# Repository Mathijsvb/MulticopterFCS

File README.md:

# About the project

MulticopterFCS is a flight controller build from the ground up. It is meant to be a development platform mainly focused on autonomous indoor flying of multi-rotor drones. 

> **Warning**
> The current version still contains design errors.

|Diagram|Board|
|---|---|
|||

# Key features

**On board:**
* High performance MCU (STM32H743 running up to 480 MHz)
* Accelerometer and gyro (MPU6000)
* Magnetometer (HMC5883L)
* Pressure and temperature sensor (BMP388)
* 64-Kbit of F-RAM (FM24C64B)
* 2x RGB LED

**Connectors:**

| **quantity** 	| **purpose**  	| **connector type**           	| **Comment**                                                           |
|----------	|----------	|--------------------------	|----------------------------------------------------------------------	|
| 1        	| SWD/JTAG 	| 1.27 mm pitch 10-pin     	| For programming and debugging                                        	|
| 1        	| SDIO     	| Micro SD Card            	| For logging data during the flight                                   	|
| 1        	| I²C      	| JST SH 4-pin             	| External I²C connector                                               	|
| 2        	| UART     	| JST SH 4-pin             	| External UART connector                                              	|
| 1        	| Battery  	| JST SH 2-pin             	| Used to measure battery voltage                                      	|
| 1        	| LED	  	| JST SH 8-pin             	| To control external LEDs                                      	|
| 1        	| IBUS     	| 2.54 mm pitch header     	| IBUS used by external receivers to communicate remote control signals |
| 6        	| PWM      	| 2.54 mm pitch header     	| PWM is used to control external ESC's                                	|
| 1        	| Buzzer   	| 2.54 mm pitch header     	| For connecting a buzzer                                              	|
| 1        	| RPLiDAR  	| 2.50 mm MOLEX SPOX 7-pin 	| This connector will be used for the RPLiDAR                          	|
| 2        	| USB      	| USB Mini B               	| USB1 goes directly to the MCU, USB2 gets converted to serial first   	|

# Roadmap:

1. ✔️ Project orientation
2. ✔️ Deciding on components
3. ✔️ Creating schematic
4. ✔️ Routing PCB
5. ✔️ Manufacturing the PCB
6.  Testing
	1. ✔️ Programming MCU
	2. ❌ Gyro/Accelerometer
		1.  ✔️ Find a the reason for to the Gyro/Accelerometer not working
		*   The MPU-6000 seems to need the ability to toggle CS which the current board does not support. Board revision is needed.
		2. Pick new Gyro/Accelerometer
	3. ❌ Magnetometer
		* Can't be detected with an I2C scanner, probably dead.
	4. Barometric pressure sensor
		1. ✔️ Check if it can be found with the I2C scanner.
		2. Check is values are sensible.
	5. ❌ On board F-RAM
		* Wrong IC choice on my part.
	6. ESC control
	7. IBUS communication
	8. Buzzer
	9. ✔️ LEDs
7. Writing drivers
	1. Gyro/Accelerometer
	2. Magnetometer
	3. Barometric pressure sensor
	4. On board F-RAM
	5. ESC control
	6. IBUS communication
	7. Buzzer and LEDs
	8. SD Card
	9. USB
8. Signal processing
	1. Data conversion and correction
	2. Data filtering
	3. Extended Kalman filter implementation for sensor fusion
	4. PI(D) controller
9. FSM controller 
10. Data logging on the SD Card

Future goals on the roadmap are likely to be Simultaneous Localization and Mapping using a LiDAR implementation. Based on this, autonomous indoor flight could be developed.

# Licensing

**This system is still a work in progress, use anything inside this repository at your own risk.**

This an open source project released under the BSD 3-Clause License.

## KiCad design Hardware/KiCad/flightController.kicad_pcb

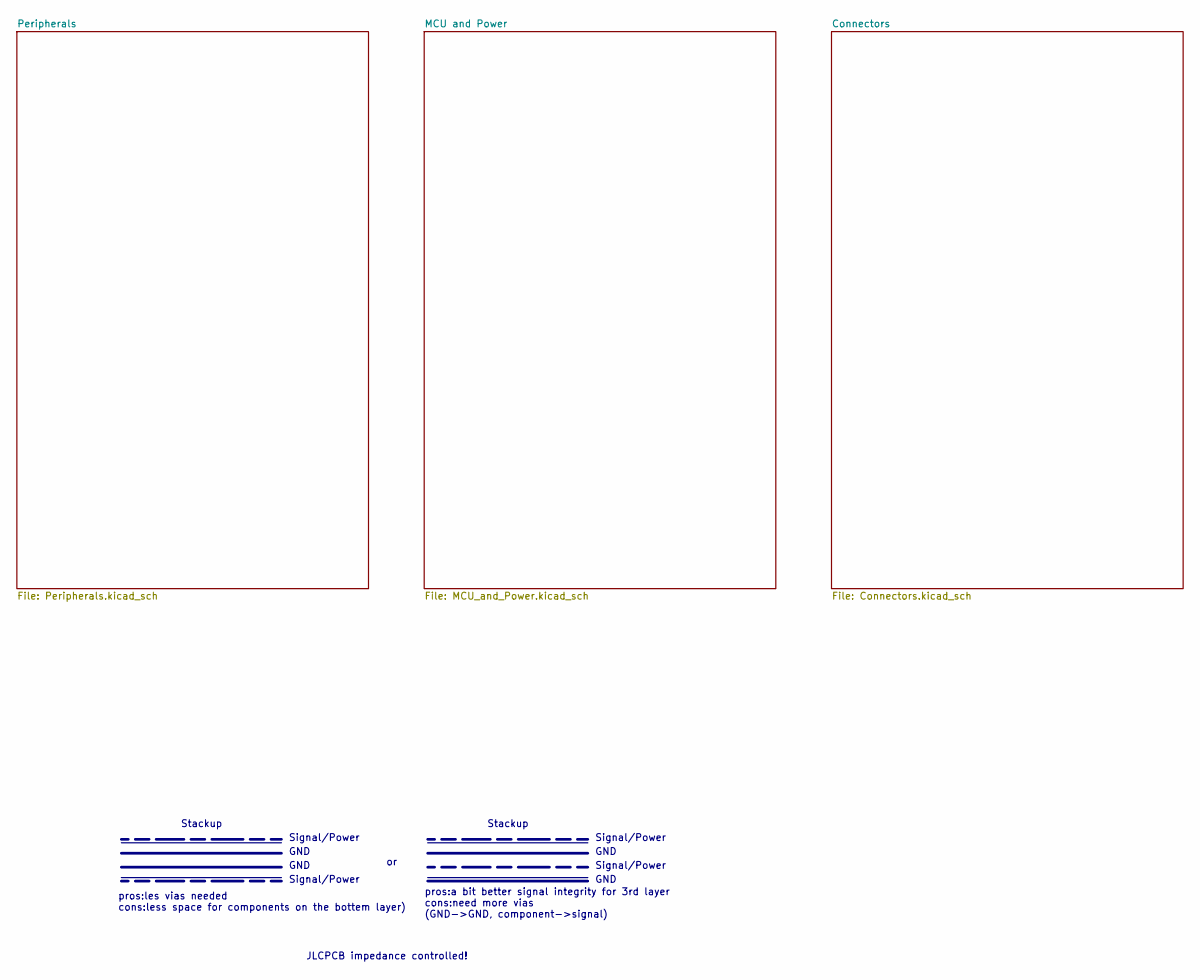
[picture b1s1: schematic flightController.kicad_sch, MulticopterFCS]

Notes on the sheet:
GND
Stackup
pros:les vias needed cons:less space for components on the bottem layer)
JLCPCB impedance controlled!
pros:a bit better signal integrity for 3rd layer cons:need more vias (GND->GND, component->signal)
Signal/Power

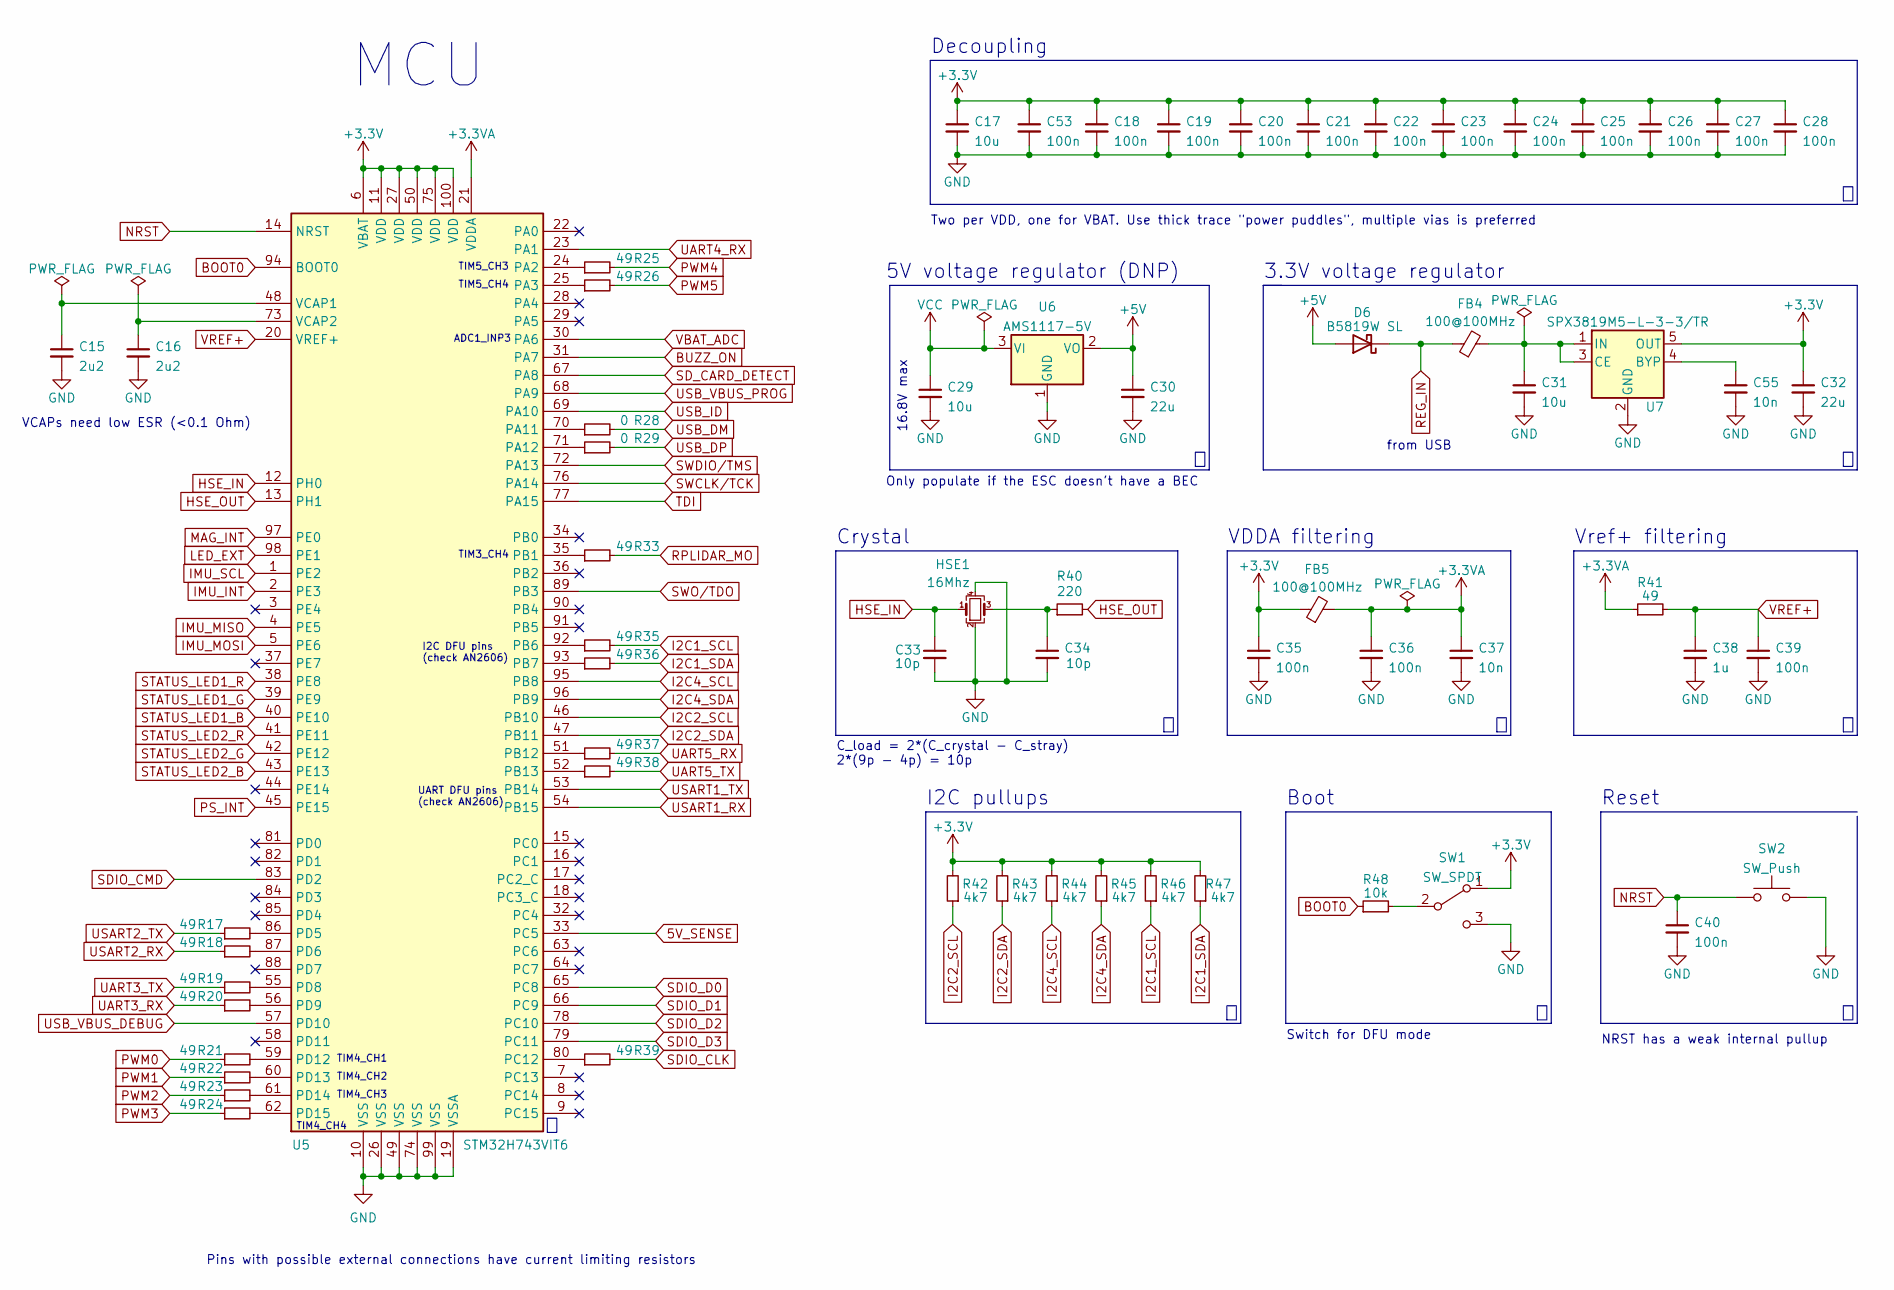
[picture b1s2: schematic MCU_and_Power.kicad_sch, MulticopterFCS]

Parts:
C15, C16: 2u2; C_0402_1005Metric; JLCPCB Part# C12530
C17, C29, C31: 10u; C_0603_1608Metric; JLCPCB Part# C96446
C18, C19, C20, C21, C22, C23, C24, C25, C26, C27, C28, C35, C36, C39, C40, C53: 100n; C_0402_1005Metric; JLCPCB Part# C1525
C30, C32: 22u; C_0603_1608Metric; JLCPCB Part# C59461
C33, C34: 10p; C_0402_1005Metric; JLCPCB Part# C32949
C37, C55: 10n; C_0402_1005Metric; JLCPCB Part# C15195
C38: 1u; C_0603_1608Metric; JLCPCB Part# C15849
D6: B5819W SL; D_SOD-123; JLCPCB Part# C8598
FB4, FB5: 100@100MHz; L_0603_1608Metric; JLCPCB Part# DNP
HSE1: 16Mhz; Crystal_SMD_3225-4Pin_3.2x2.5mm; JLCPCB Part# C13738
R17, R18, R19, R20, R21, R22, R23, R24, R25, R26, R33, R35, R36, R37, R38, R39, R41: 49; R_0402_1005Metric
R28, R29: 0; R_0402_1005Metric
R40: 220; R_0402_1005Metric
R42, R43, R44, R45, R46, R47: 4k7; R_0402_1005Metric
R48: 10k; R_0402_1005Metric
SW1: SW_SPDT; SW_SPDT_PCM12; JLCPCB Part# DNP
SW2: SW_Push; SW_SPST_FSMSM; JLCPCB Part# DNP
U5: STM32H743VIT6; LQFP-100_14x14mm_P0.5mm; JLCPCB Part# DNP
U6: AMS1117-5V; SOT-223-3_TabPin2; JLCPCB Part# DNP
U7: SPX3819M5-L-3-3/TR; SOT-23-5; JLCPCB Part# DNP

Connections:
5V_SENSE: U5.33 (PC5); also elsewhere on the board
+3.3VA: C36.1, C37.1, FB5.2, R41.1, U5.21 (VDDA)
+3V3: C17.1, C18.1, C19.1, C20.1, C21.1, C22.1, C23.1, C24.1, C25.1, C26.1, C27.1, C28.1, C32.1, C35.1, C53.1, FB5.1, R42.2, R43.2, R44.2, R45.2, R46.2, R47.2, SW1.1 (A), U5.6 (VBAT), U5.11 (VDD), U5.27 (VDD), U5.50 (VDD), U5.75 (VDD), U5.100 (VDD), U7.5 (OUT); also elsewhere on the board
+5V: C30.1, D6.2 (A), U6.2 (VO); also elsewhere on the board
BOOT0: R48.1, U5.94 (BOOT0)
BUZZ_ON: U5.31 (PA7); also elsewhere on the board
GND: C15.2, C16.2, C17.2, C18.2, C19.2, C20.2, C21.2, C22.2, C23.2, C24.2, C25.2, C26.2, C27.2, C28.2, C29.2, C30.2, C31.2, C32.2, C33.2, C34.2, C35.2, C36.2, C37.2, C38.2, C39.2, C40.2, C53.2, C55.2, HSE1.2, HSE1.4, SW1.3 (C), SW2.2, U5.10 (VSS), U5.19 (VSSA), U5.26 (VSS), U5.49 (VSS), U5.74 (VSS), U5.99 (VSS), U6.1 (GND), U7.2 (GND); also elsewhere on the board
HSE_IN: C33.1, HSE1.1, U5.12 (PH0)
HSE_OUT: R40.2, U5.13 (PH1)
I2C1_SCL: R35.2, R46.1; also elsewhere on the board
I2C1_SDA: R36.2, R47.1; also elsewhere on the board
I2C2_SCL: R42.1, U5.46 (PB10); also elsewhere on the board
I2C2_SDA: R43.1, U5.47 (PB11); also elsewhere on the board
I2C4_SCL: R44.1, U5.95 (PB8); also elsewhere on the board
I2C4_SDA: R45.1, U5.96 (PB9); also elsewhere on the board
IMU_INT: U5.2 (PE3); also elsewhere on the board
IMU_MISO: U5.4 (PE5); also elsewhere on the board
IMU_MOSI: U5.5 (PE6); also elsewhere on the board
IMU_SCL: U5.1 (PE2); also elsewhere on the board
LED_EXT: U5.98 (PE1); also elsewhere on the board
MAG_INT: U5.97 (PE0); also elsewhere on the board
NRST: C40.1, SW2.1, U5.14 (NRST); also elsewhere on the board
unnamed: C15.1, U5.48 (VCAP1)
unnamed: C16.1, U5.73 (VCAP2)
unnamed: C31.1, FB4.2, U7.1 (IN), U7.3 (CE)
unnamed: C34.1, HSE1.3, R40.1
unnamed: C55.1, U7.4 (BYP)
unnamed: R17.2, U5.86 (PD5)
unnamed: R18.2, U5.87 (PD6)
unnamed: R19.2, U5.55 (PD8)
unnamed: R20.2, U5.56 (PD9)
unnamed: R21.2, U5.59 (PD12)
unnamed: R22.2, U5.60 (PD13)
unnamed: R23.2, U5.61 (PD14)
unnamed: R24.2, U5.62 (PD15)
unnamed: R25.1, U5.24 (PA2)
unnamed: R26.1, U5.25 (PA3)
unnamed: R28.1, U5.70 (PA11)
unnamed: R29.1, U5.71 (PA12)
unnamed: R33.1, U5.35 (PB1)
unnamed: R35.1, U5.92 (PB6)
unnamed: R36.1, U5.93 (PB7)
unnamed: R37.1, U5.51 (PB12)
unnamed: R38.1, U5.52 (PB13)
unnamed: R39.1, U5.80 (PC12)
unnamed: R48.2, SW1.2 (B)
PS_INT: U5.45 (PE15); also elsewhere on the board
PWM0: R21.1; also elsewhere on the board
PWM1: R22.1; also elsewhere on the board
PWM2: R23.1; also elsewhere on the board
PWM3: R24.1; also elsewhere on the board
PWM4: R25.2; also elsewhere on the board
PWM5: R26.2; also elsewhere on the board
REG_IN: D6.1 (K), FB4.1; also elsewhere on the board
RPLIDAR_MO: R33.2; also elsewhere on the board
SDIO_CLK: R39.2; also elsewhere on the board
SDIO_CMD: U5.83 (PD2); also elsewhere on the board
SDIO_D0: U5.65 (PC8); also elsewhere on the board
SDIO_D1: U5.66 (PC9); also elsewhere on the board
SDIO_D2: U5.78 (PC10); also elsewhere on the board
SDIO_D3: U5.79 (PC11); also elsewhere on the board
SD_CARD_DETECT: U5.67 (PA8); also elsewhere on the board
STATUS_LED1_B: U5.40 (PE10); also elsewhere on the board
STATUS_LED1_G: U5.39 (PE9); also elsewhere on the board
STATUS_LED1_R: U5.38 (PE8); also elsewhere on the board
STATUS_LED2_B: U5.43 (PE13); also elsewhere on the board
STATUS_LED2_G: U5.42 (PE12); also elsewhere on the board
STATUS_LED2_R: U5.41 (PE11); also elsewhere on the board
SWCLK/TCK: U5.76 (PA14); also elsewhere on the board
SWDIO/TMS: U5.72 (PA13); also elsewhere on the board
SWO/TDO: U5.89 (PB3); also elsewhere on the board
TDI: U5.77 (PA15); also elsewhere on the board
UART3_RX: R20.1; also elsewhere on the board
UART3_TX: R19.1; also elsewhere on the board
UART4_RX: U5.23 (PA1); also elsewhere on the board
UART5_RX: R37.2; also elsewhere on the board
UART5_TX: R38.2; also elsewhere on the board
USART1_RX: U5.54 (PB15); also elsewhere on the board
USART1_TX: U5.53 (PB14); also elsewhere on the board
USART2_RX: R18.1; also elsewhere on the board
USART2_TX: R17.1; also elsewhere on the board
USB_DM: R28.2; also elsewhere on the board
USB_DP: R29.2; also elsewhere on the board
USB_ID: U5.69 (PA10); also elsewhere on the board
USB_VBUS_DEBUG: U5.57 (PD10); also elsewhere on the board
USB_VBUS_PROG: U5.68 (PA9); also elsewhere on the board
VBAT_ADC: U5.30 (PA6); also elsewhere on the board
VCC: C29.1, U6.3 (VI); also elsewhere on the board
VREF+: C38.1, C39.1, R41.2, U5.20 (VREF+)

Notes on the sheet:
Boot
Reset
ADC1_INP3
TIM5_CH3
from USB
3.3V voltage regulator
TIM4_CH3
Vref+ filtering
Pins with possible external connections have current limiting resistors
5V voltage regulator (DNP)
UART DFU pins (check AN2606)
VCAPs need low ESR (<0.1 Ohm)
VDDA filtering
Decoupling
16.8V max
I2C pullups
TIM4_CH4
NRST has a weak internal pullup
Crystal
TIM4_CH2
TIM4_CH1
MCU
Two per VDD, one for VBAT. Use thick trace "power puddles", multiple vias is preferred
I2C DFU pins (check AN2606)
Switch for DFU mode
TIM5_CH4
Only populate if the ESC doesn't have a BEC
C_load = 2*(C_crystal - C_stray) 2*(9p - 4p) = 10p
TIM3_CH4

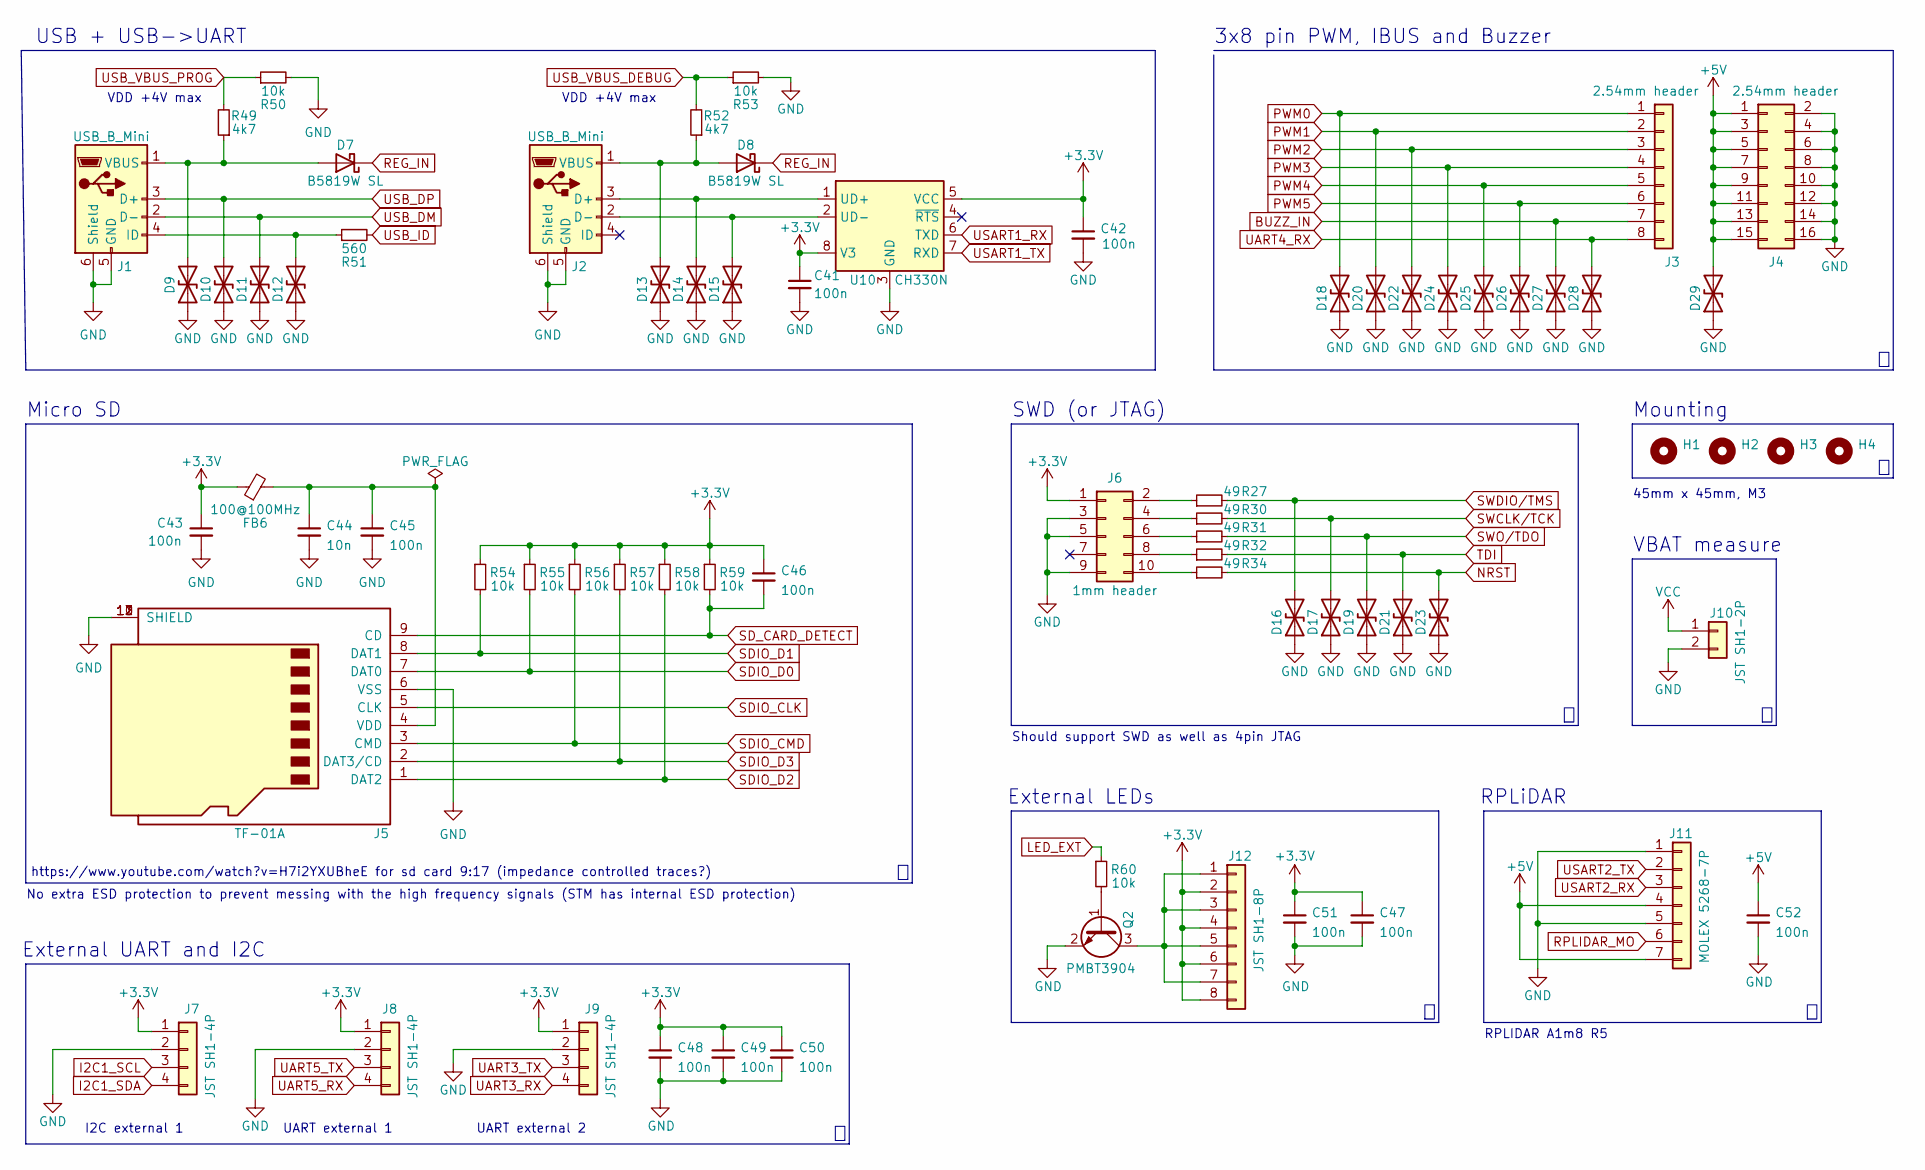
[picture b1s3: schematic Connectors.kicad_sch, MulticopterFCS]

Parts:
C41, C42, C43, C45, C46, C47, C48, C49, C50, C51, C52: 100n; C_0402_1005Metric; JLCPCB Part# C1525
C44: 10n; C_0402_1005Metric; JLCPCB Part# C15195
D7, D8: B5819W SL; D_SOD-123; JLCPCB Part# C8598
D9, D10, D11, D12, D13, D14, D15, D16, D17, D18, D19, D20, D21, D22, D23, D24, D25, D26, D27, D28, D29: LXES15AAA1-133; R_0402_1005Metric
FB6: 100@100MHz; L_0603_1608Metric; JLCPCB Part# DNP
H1, H2, H3, H4: MountingHole; MountingHole_3.2mm_M3_ISO14580_Pad; JLCPCB Part# DNP
J1, J2: USB_B_Mini; USB_Mini-B_Wuerth_65100516121_Horizontal; JLCPCB Part# DNP
J3: 2.54mm header; PinHeader_1x08_P2.54mm_Vertical_lessSilk; JLCPCB Part# DNP
J4: 2.54mm header; PinHeader_2x08_P2.54mm_Horizontal_lessSilk; JLCPCB Part# DNP
J5: TF-01A; JLCPCB Part# DNP
J6: 1mm header; PinHeader_2x05_P1.27mm_Vertical_SMD; JLCPCB Part# DNP
J7, J8, J9: JST SH1-4P; JST_SH_SM04B-SRSS-TB_1x04-1MP_P1.00mm_Horizontal; JLCPCB Part# DNP
J10: JST SH1-2P; JST_SHL_SM02B-SHLS-TF_1x02-1MP_P1.00mm_Horizontal; JLCPCB Part# DNP
J11: MOLEX 5268-7P; Molex_SPOX_5268-07A_1x07_P2.50mm_Horizontal; JLCPCB Part# DNP
J12: JST SH1-8P; JST_SH_SM08B-SRSS-TB_1x08-1MP_P1.00mm_Horizontal; JLCPCB Part# DNP
Q2: PMBT3904; SOT-23; JLCPCB Part# DNP
R27, R30, R31, R32, R34: 49; R_0402_1005Metric
R49, R52: 4k7; R_0402_1005Metric
R50, R53, R54, R55, R56, R57, R58, R59, R60: 10k; R_0402_1005Metric
R51: 560; R_0402_1005Metric
U10: CH330N; SOP-8_3.9x4.9mm_P1.27mm; JLCPCB Part# C108996

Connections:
+3V3: C41.1, C42.1, C43.1, C46.1, C47.1, C48.1, C49.1, C50.1, C51.1, FB6.1, J6.1, J7.1, J8.1, J9.1, J12.2, J12.4, J12.6, J12.8, R54.1, R55.1, R56.1, R57.1, R58.1, R59.1, U10.5 (VCC), U10.8 (V3); also elsewhere on the board
+5V: C52.1, D29.2 (A2), J4.1, J4.3, J4.5, J4.7, J4.9, J4.11, J4.13, J4.15, J11.4, J11.7; also elsewhere on the board
BUZZ_IN: D27.2 (A2), J3.7; also elsewhere on the board
GND: C41.2, C42.2, C43.2, C44.2, C45.2, C47.2, C48.2, C49.2, C50.2, C51.2, C52.2, D9.1 (A1), D10.1 (A1), D11.1 (A1), D12.1 (A1), D13.1 (A1), D14.1 (A1), D15.1 (A1), D16.1 (A1), D17.1 (A1), D18.1 (A1), D19.1 (A1), D20.1 (A1), D21.1 (A1), D22.1 (A1), D23.1 (A1), D24.1 (A1), D25.1 (A1), D26.1 (A1), D27.1 (A1), D28.1 (A1), D29.1 (A1), J1.5 (GND), J1.6 (Shield), J2.5 (GND), J2.6 (Shield), J4.2, J4.4, J4.6, J4.8, J4.10, J4.12, J4.14, J4.16, J5.6 (VSS), J5.10 (SHIELD), J5.11 (SHIELD), J5.12 (SHIELD), J5.13 (SHIELD), J6.3, J6.5, J6.9, J7.2, J8.2, J9.2, J10.2, J11.1, J11.5, Q2.2 (E), R50.2, R53.2, U10.3 (GND); also elsewhere on the board
I2C1_SCL: J7.3; also elsewhere on the board
I2C1_SDA: J7.4; also elsewhere on the board
LED_EXT: R60.1; also elsewhere on the board
NRST: D23.2 (A2), R34.2; also elsewhere on the board
unnamed: C44.1, C45.1, FB6.2, J5.4 (VDD)
unnamed: D7.2 (A), D9.2 (A2), J1.1 (VBUS), R49.1
unnamed: D8.2 (A), D13.2 (A2), J2.1 (VBUS), R52.1
unnamed: D12.2 (A2), J1.4 (ID), R51.1
unnamed: D15.2 (A2), J2.2 (D-), U10.2 (UD-)
unnamed: D14.2 (A2), J2.3 (D+), U10.1 (UD+)
unnamed: J6.2, R27.1
unnamed: J6.4, R30.1
unnamed: J6.6, R31.1
unnamed: J6.8, R32.1
unnamed: J6.10, R34.1
unnamed: J12.1, J12.3, J12.5, J12.7, Q2.3 (C)
unnamed: Q2.1 (B), R60.2
PWM0: D18.2 (A2), J3.1; also elsewhere on the board
PWM1: D20.2 (A2), J3.2; also elsewhere on the board
PWM2: D22.2 (A2), J3.3; also elsewhere on the board
PWM3: D24.2 (A2), J3.4; also elsewhere on the board
PWM4: D25.2 (A2), J3.5; also elsewhere on the board
PWM5: D26.2 (A2), J3.6; also elsewhere on the board
REG_IN: D7.1 (K), D8.1 (K); also elsewhere on the board
RPLIDAR_MO: J11.6; also elsewhere on the board
SDIO_CLK: J5.5 (CLK); also elsewhere on the board
SDIO_CMD: J5.3 (CMD), R56.2; also elsewhere on the board
SDIO_D0: J5.7 (DAT0), R55.2; also elsewhere on the board
SDIO_D1: J5.8 (DAT1), R54.2; also elsewhere on the board
SDIO_D2: J5.1 (DAT2), R58.2; also elsewhere on the board
SDIO_D3: J5.2 (DAT3/CD), R57.2; also elsewhere on the board
SD_CARD_DETECT: C46.2, J5.9 (CD), R59.2; also elsewhere on the board
SWCLK/TCK: D17.2 (A2), R30.2; also elsewhere on the board
SWDIO/TMS: D16.2 (A2), R27.2; also elsewhere on the board
SWO/TDO: D19.2 (A2), R31.2; also elsewhere on the board
TDI: D21.2 (A2), R32.2; also elsewhere on the board
UART3_RX: J9.4; also elsewhere on the board
UART3_TX: J9.3; also elsewhere on the board
UART4_RX: D28.2 (A2), J3.8; also elsewhere on the board
UART5_RX: J8.4; also elsewhere on the board
UART5_TX: J8.3; also elsewhere on the board
USART1_RX: U10.6 (TXD); also elsewhere on the board
USART1_TX: U10.7 (RXD); also elsewhere on the board
USART2_RX: J11.3; also elsewhere on the board
USART2_TX: J11.2; also elsewhere on the board
USB_DM: D11.2 (A2), J1.2 (D-); also elsewhere on the board
USB_DP: D10.2 (A2), J1.3 (D+); also elsewhere on the board
USB_ID: R51.2; also elsewhere on the board
USB_VBUS_DEBUG: R52.2, R53.1; also elsewhere on the board
USB_VBUS_PROG: R49.2, R50.1; also elsewhere on the board
VCC: J10.1; also elsewhere on the board

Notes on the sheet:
https://www.youtube.com/watch?v=H7i2YXUBheE for sd card 9:17 (impedance controlled traces?)
RPLiDAR
Mounting
External LEDs
UART external 2
External UART and I2C
Micro SD
VDD +4V max
3x8 pin PWM, IBUS and Buzzer
No extra ESD protection to prevent messing with the high frequency signals (STM has internal ESD protection)
I2C external 1
45mm x 45mm, M3
RPLIDAR A1m8 R5
Should support SWD as well as 4pin JTAG
VBAT measure
SWD (or JTAG)
USB + USB->UART
UART external 1

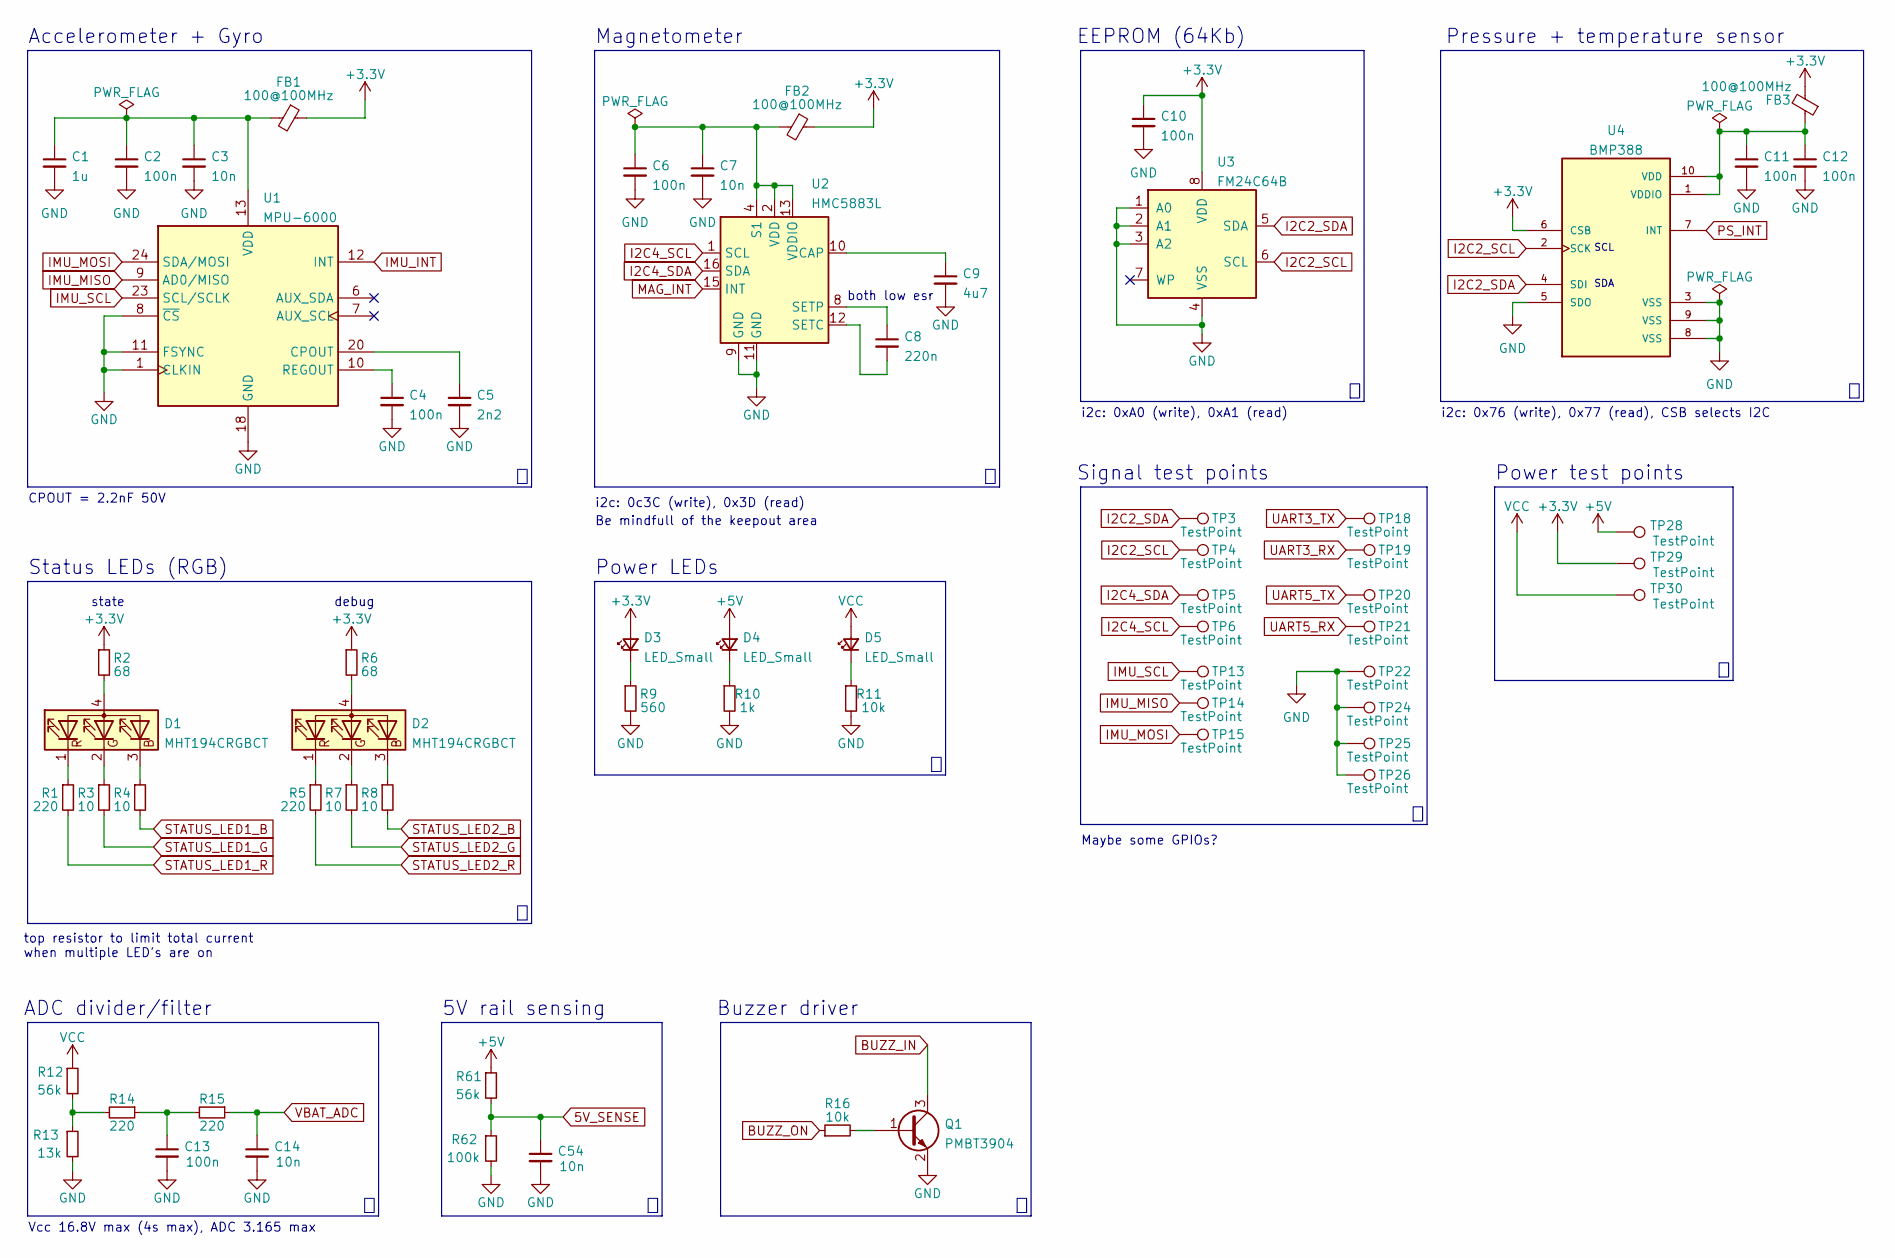
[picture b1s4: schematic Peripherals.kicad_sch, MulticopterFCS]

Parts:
C1: 1u; C_0603_1608Metric; JLCPCB Part# C15849
C2, C4, C6, C10, C11, C12, C13: 100n; C_0402_1005Metric; JLCPCB Part# C1525
C3, C7, C14, C54: 10n; C_0402_1005Metric; JLCPCB Part# C15195
C5: 2n2; C_0402_1005Metric; JLCPCB Part# C1531
C8: 220n; C_0603_1608Metric; JLCPCB Part# C21120
C9: 4u7; C_0603_1608Metric; JLCPCB Part# C19666
D1, D2: MHT194CRGBCT; 0605; JLCPCB Part# DNP
D3, D4, D5: LED_Small; LED_0603_1608Metric; JLCPCB Part# DNP
FB1, FB2, FB3: 100@100MHz; L_0603_1608Metric; JLCPCB Part# DNP
Q1: PMBT3904; SOT-23; JLCPCB Part# DNP
R1, R5, R14, R15: 220; R_0402_1005Metric
R2, R6: 68; R_0603_1608Metric
R3, R4, R7, R8: 10; R_0402_1005Metric
R9: 560; R_0603_1608Metric
R10: 1k; R_0603_1608Metric
R11: 10k; R_0603_1608Metric
R12, R61: 56k; R_0402_1005Metric
R13: 13k; R_0402_1005Metric
R16: 10k; R_0402_1005Metric
R62: 100k; R_0402_1005Metric
TP3, TP4, TP5, TP6, TP13, TP14, TP15, TP18, TP19, TP20, TP21, TP22, TP24, TP25, TP26, TP28, TP29, TP30: TestPoint; TestPoint_Pad_D1.0mm; JLCPCB Part# DNP
U1: MPU-6000; InvenSense_QFN-24_4x4mm_P0.5mm; JLCPCB Part# DNP
U2: HMC5883L; LGA-16_3x3mm_P0.5mm_Large_Pads; JLCPCB Part# DNP
U3: FM24C64B; SOIC-8_3.9x4.9mm_P1.27mm; JLCPCB Part# DNP
U4: BMP388; PQFN50P200X200X80-10N; JLCPCB Part# C779278

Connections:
5V_SENSE: C54.1, R61.2, R62.1; also elsewhere on the board
+3V3: C10.1, D3.2 (A), FB1.1, FB2.1, FB3.2, R2.1, R6.1, TP29.1, U3.8 (VDD), U4.6 (CSB); also elsewhere on the board
+5V: D4.2 (A), R61.1, TP28.1; also elsewhere on the board
BUZZ_IN: Q1.3 (C); also elsewhere on the board
BUZZ_ON: R16.1; also elsewhere on the board
GND: C1.2, C2.2, C3.2, C4.2, C5.2, C6.2, C7.2, C9.2, C10.2, C11.2, C12.2, C13.2, C14.2, C54.2, Q1.2 (E), R9.2, R10.2, R11.2, R13.2, R62.2, TP22.1, TP24.1, TP25.1, TP26.1, U1.1 (CLKIN), U1.8 (~CS), U1.11 (FSYNC), U1.18 (GND), U2.9 (GND), U2.11 (GND), U3.1 (A0), U3.2 (A1), U3.3 (A2), U3.4 (VSS), U4.3 (VSS), U4.5 (SDO), U4.8 (VSS), U4.9 (VSS); also elsewhere on the board
I2C2_SCL: TP4.1, U3.6 (SCL), U4.2 (SCK); also elsewhere on the board
I2C2_SDA: TP3.1, U3.5 (SDA), U4.4 (SDI); also elsewhere on the board
I2C4_SCL: TP6.1, U2.1 (SCL); also elsewhere on the board
I2C4_SDA: TP5.1, U2.16 (SDA); also elsewhere on the board
IMU_INT: U1.12 (INT); also elsewhere on the board
IMU_MISO: TP14.1, U1.9 (AD0/MISO); also elsewhere on the board
IMU_MOSI: TP15.1, U1.24 (SDA/MOSI); also elsewhere on the board
IMU_SCL: TP13.1, U1.23 (SCL/SCLK); also elsewhere on the board
MAG_INT: U2.15 (INT); also elsewhere on the board
unnamed: C1.1, C2.1, C3.1, FB1.2, U1.13 (VDD)
unnamed: C4.1, U1.10 (REGOUT)
unnamed: C5.1, U1.20 (CPOUT)
unnamed: C6.1, C7.1, FB2.2, U2.2 (VDD), U2.4 (S1), U2.13 (VDDIO)
unnamed: C8.1, U2.8 (SETP)
unnamed: C8.2, U2.12 (SETC)
unnamed: C9.1, U2.10 (CAP)
unnamed: C11.1, C12.1, FB3.1, U4.1 (VDDIO), U4.10 (VDD)
unnamed: C13.1, R14.1, R15.2
unnamed: D1.1 (RK), R1.1
unnamed: D1.2 (GK), R3.1
unnamed: D1.3 (BK), R4.1
unnamed: D1.4 (A), R2.2
unnamed: D2.1 (RK), R5.1
unnamed: D2.2 (GK), R7.1
unnamed: D2.3 (BK), R8.1
unnamed: D2.4 (A), R6.2
unnamed: D3.1 (K), R9.1
unnamed: D4.1 (K), R10.1
unnamed: D5.1 (K), R11.1
unnamed: Q1.1 (B), R16.2
unnamed: R12.2, R13.1, R14.2
PS_INT: U4.7 (INT); also elsewhere on the board
STATUS_LED1_B: R4.2; also elsewhere on the board
STATUS_LED1_G: R3.2; also elsewhere on the board
STATUS_LED1_R: R1.2; also elsewhere on the board
STATUS_LED2_B: R8.2; also elsewhere on the board
STATUS_LED2_G: R7.2; also elsewhere on the board
STATUS_LED2_R: R5.2; also elsewhere on the board
UART3_RX: TP19.1; also elsewhere on the board
UART3_TX: TP18.1; also elsewhere on the board
UART5_RX: TP21.1; also elsewhere on the board
UART5_TX: TP20.1; also elsewhere on the board
VBAT_ADC: C14.1, R15.1; also elsewhere on the board
VCC: D5.2 (A), R12.1, TP30.1; also elsewhere on the board

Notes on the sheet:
SCL
ADC divider/filter
5V rail sensing
Signal test points
Buzzer driver
top resistor to limit total current when multiple LED's are on
Power LEDs
Maybe some GPIOs?
i2c: 0x76 (write), 0x77 (read), CSB selects I2C
Magnetometer
SDA
both low esr
EEPROM (64Kb)
i2c: 0c3C (write), 0x3D (read)
debug
i2c: 0xA0 (write), 0xA1 (read)
CPOUT = 2.2nF 50V
Pressure + temperature sensor
Be mindfull of the keepout area
Status LEDs (RGB)
Accelerometer + Gyro
Vcc 16.8V max (4s max), ADC 3.165 max
Power test points
state

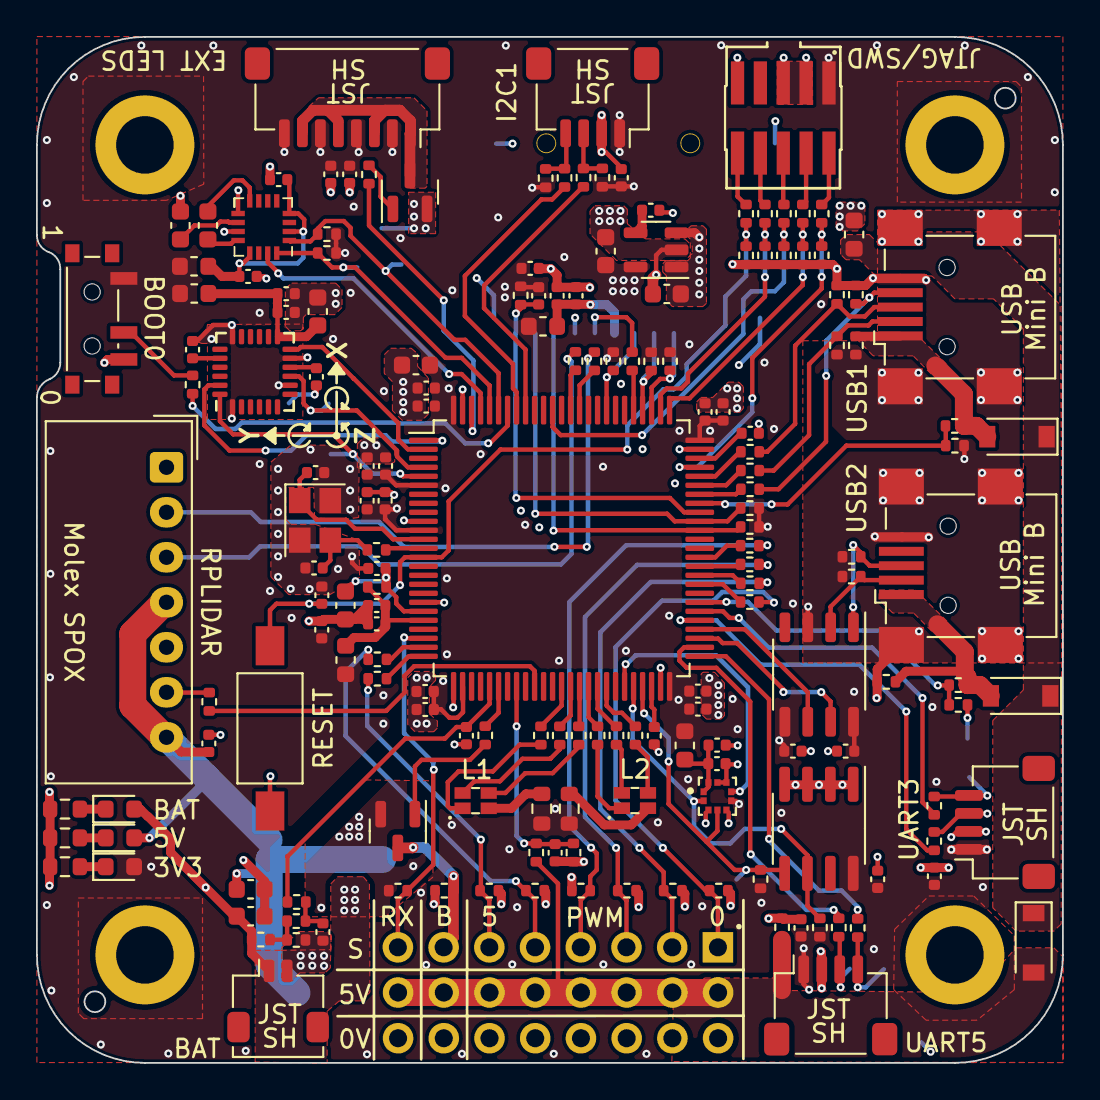
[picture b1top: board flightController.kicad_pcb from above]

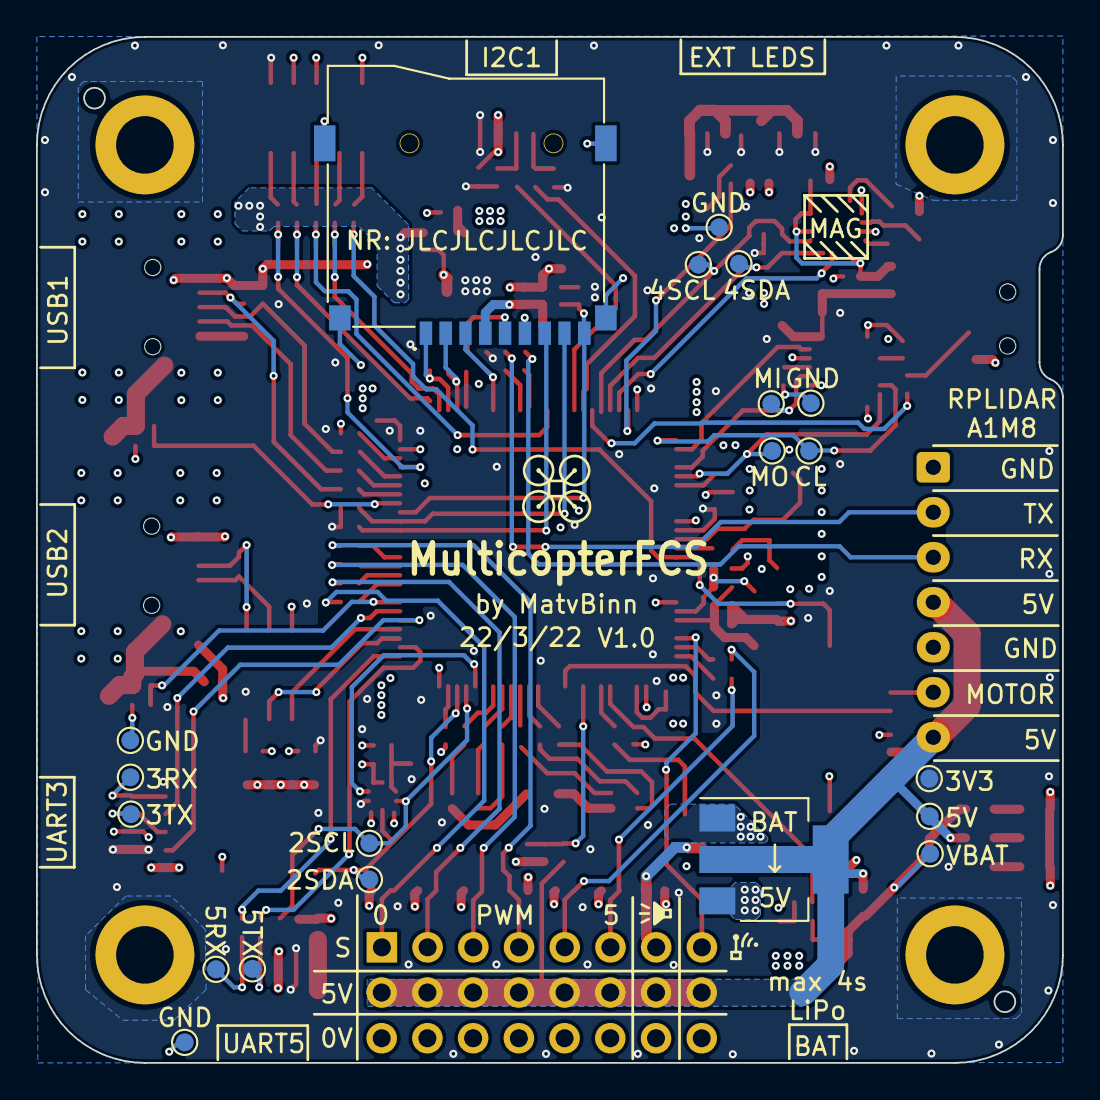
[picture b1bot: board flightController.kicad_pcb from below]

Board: 4 copper layers, 57.0 x 57.0 mm, 199 parts (20 on the bottom side), 125 nets.

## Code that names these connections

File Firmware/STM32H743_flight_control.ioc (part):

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Mcu.Name=STM32H743VITx
Mcu.Package=LQFP100
Mcu.UserName=STM32H743VITx
PA0.Mode=Asynchronous
PA0.Signal=UART4_TX
PA1.Mode=Asynchronous
PA1.Signal=UART4_RX
PA10.Mode=OTG/Dual_Role_Device
PA10.Signal=USB_OTG_FS_ID
PA11.Mode=OTG/Dual_Role_Device
PA11.Signal=USB_OTG_FS_DM
PA12.Mode=OTG/Dual_Role_Device
PA12.Signal=USB_OTG_FS_DP
PA13\ (JTMS/SWDIO).Mode=JTAG_4_pins
PA13\ (JTMS/SWDIO).Signal=DEBUG_JTMS-SWDIO
PA14\ (JTCK/SWCLK).Mode=JTAG_4_pins
PA14\ (JTCK/SWCLK).Signal=DEBUG_JTCK-SWCLK
PA15\ (JTDI).Mode=JTAG_4_pins
PA15\ (JTDI).Signal=DEBUG_JTDI
PA2.Signal=S_TIM5_CH3
PA3.Signal=S_TIM5_CH4
PA6.Signal=ADCx_INP3
PA7.GPIOParameters=GPIO_Label
PA7.GPIO_Label=BUZZ_ON
PA7.Signal=GPIO_Output
PA8.GPIOParameters=GPIO_Label
PA8.GPIO_Label=SD_CARD_DETECT
PA8.Signal=GPIO_Input
PA9.Mode=Activate_VBUS
PA9.Signal=USB_OTG_FS_VBUS
PB1.Signal=S_TIM3_CH4
PB10.Mode=I2C
PB10.Signal=I2C2_SCL
PB11.Mode=I2C
PB11.Signal=I2C2_SDA
PB12.Mode=Asynchronous
PB12.Signal=UART5_RX
PB13.Mode=Asynchronous
PB13.Signal=UART5_TX
PB14.Mode=Asynchronous
PB14.Signal=USART1_TX
PB15.Mode=Asynchronous
PB15.Signal=USART1_RX
PB3\ (JTDO/TRACESWO).Mode=JTAG_4_pins
PB3\ (JTDO/TRACESWO).Signal=DEBUG_JTDO-SWO
PB6.Mode=I2C
PB6.Signal=I2C1_SCL
PB7.Mode=I2C
PB7.Signal=I2C1_SDA
PB8.Mode=I2C
PB8.Signal=I2C4_SCL
PB9.Mode=I2C
PB9.Signal=I2C4_SDA
PD10.GPIOParameters=GPIO_Label
PD10.GPIO_Label=USB_VBUS_DEBUG
PD10.Signal=GPIO_Input
PD12.Signal=S_TIM4_CH1
PD13.Signal=S_TIM4_CH2
PD14.Signal=S_TIM4_CH3
PD15.Signal=S_TIM4_CH4
PD5.Mode=Asynchronous
PD5.Signal=USART2_TX
PD6.Mode=Asynchronous
PD6.Signal=USART2_RX
PD8.Mode=Asynchronous
PD8.Signal=USART3_TX
PD9.Mode=Asynchronous
PD9.Signal=USART3_RX
PE0.GPIOParameters=GPIO_Label
PE0.GPIO_Label=MAG_INT
PE0.Signal=GPIO_Input
PE1.GPIOParameters=GPIO_Label
PE1.GPIO_Label=LED_EXT
PE1.Signal=GPIO_Output
PE10.GPIOParameters=GPIO_Label
PE10.GPIO_Label=STATUS_LED1_B
PE10.Signal=GPIO_Output
PE11.GPIOParameters=GPIO_Label
PE11.GPIO_Label=STATUS_LED2_R
PE11.Signal=GPIO_Output
PE12.GPIOParameters=GPIO_Label
PE12.GPIO_Label=STATUS_LED2_G
PE12.Signal=GPIO_Output
PE13.GPIOParameters=GPIO_Label
PE13.GPIO_Label=STATUS_LED2_B
PE13.Signal=GPIO_Output
PE15.GPIOParameters=GPIO_Label
PE15.GPIO_Label=PS_INT
PE15.Signal=GPIO_Input
PE2.GPIOParameters=GPIO_PuPd
PE2.GPIO_PuPd=GPIO_PULLUP
PE2.Mode=Full_Duplex_Master
PE2.Signal=SPI4_SCK
PE3.GPIOParameters=GPIO_Label
PE3.GPIO_Label=IMU_INT
PE3.Signal=GPIO_Input
PE5.Mode=Full_Duplex_Master
PE5.Signal=SPI4_MISO
PE6.Mode=Full_Duplex_Master
PE6.Signal=SPI4_MOSI
PE8.GPIOParameters=GPIO_Label
PE8.GPIO_Label=STATUS_LED1_R
PE8.Signal=GPIO_Output
PE9.GPIOParameters=GPIO_Label
PE9.GPIO_Label=STATUS_LED1_G
PE9.Signal=GPIO_Output
PH0-OSC_IN\ (PH0).Mode=HSE-External-Oscillator
PH0-OSC_IN\ (PH0).Signal=RCC_OSC_IN
PH1-OSC_OUT\ (PH1).Mode=HSE-External-Oscillator
PH1-OSC_OUT\ (PH1).Signal=RCC_OSC_OUT
RCC.HSE_VALUE=16000000
RCC.SYSCLKFreq_VALUE=480000000
RCC.SYSCLKSource=RCC_SYSCLKSOURCE_PLLCLK
board=custom
